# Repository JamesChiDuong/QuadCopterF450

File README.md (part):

# QuadCopter F450 – STM32F429 Flight Controller

Firmware điều khiển quadcopter F450 trên STM32F429I-DISC1 + FreeRTOS: đọc MPU6050, ước lượng góc, PID cascade, trộn 4 motor (X), đọc tay điều khiển RC, arm/disarm và failsafe. Có lệnh UART để test motor, tune PID và xem telemetry.

> ⚠️ **AN TOÀN:** Luôn **tháo cánh quạt** khi test trên bàn, khi đổi cấu hình hoặc nạp firmware mới. Chỉ lắp cánh sau khi đã qua hết checklist ở mục 5.

---

## 0. Chọn phiên bản build

Trong `Core/Inc/USER_Config.h`:

```c
#define FC_VARIANT   FC_VARIANT_RC_FULL     // hoặc FC_VARIANT_UART_TEST, FC_VARIANT_GAMEPAD
```

| | `FC_VARIANT_RC_FULL` (1) | `FC_VARIANT_UART_TEST` (2) | `FC_VARIANT_GAMEPAD` (3) |
|---|---|---|---|
| Thiết bị điều khiển | Tay RC + receiver, RX nối PE2–PE6 | Không có, chỉ lệnh UART | **Tay cầm USB** (GameSir Nova 2 Lite ở chế độ Switch hoặc Xbox…) cắm vào **CN6** |
| Arm | Công tắc CH5 | Lệnh `@QC+ARM` | **Giữ START** 0.5 s |
| Disarm | Gạt CH5 | `@QC+DISARM` | **B** hoặc **BACK** (cả `@QC+DISARM`) |
| Điều khiển | Cần gạt RC | `@QC+SP=...` / bàn phím qua `drone_viewer.py --control` | Cần tay cầm (mục 5, bước 7c) |
| Giới hạn ga | 1850 µs | 1300 µs (chỉ test trên bàn) | 1850 µs |
| Failsafe | Mất sóng RC > 100 ms | Tùy chọn `UART_SP_TIMEOUT_MS` | **Rút / tắt tay cầm** (mất kết nối USB) |
| Màn hình | Các kênh RC | Setpoint UART | Loại tay cầm, trạng thái và vị trí cần |
| Chân dùng thêm | PE2–PE6 | — | PB13/PB14/PB15 (USB), **PC4** (bật nguồn USB) |
| Clock | HSI | HSI | **HSE 8 MHz** (USB cần clock chính xác) |

Muốn giữ nhiều phiên bản mà không phải sửa file: trong CubeIDE tạo thêm Build Configuration, rồi vào *Properties → C/C++ Build → Settings → MCU GCC Compiler → Preprocessor* thêm `FC_VARIANT=2` (hoặc `3`). Dòng lệnh: `make VARIANT=3`. Tương tự, `UI_LCD_ENABLE=0` tắt màn hình.

> ⚠️ **Bản GAMEPAD dùng PC4 để bật nguồn 5 V cho cổng USB CN6** (theo thiết kế của board DISC1). Chân này trước đây là `BLDC3_VCC`. Nếu có dây nào đang cắm vào PC4 thì **rút ra** trước khi nạp bản GAMEPAD.

---

## 1. Phần cứng

| Thành phần | Ghi chú |
|---|---|
| Khung F450, 4× motor A2212/15T 930KV | |
| 4× ESC SimonK 30A | Nhận xung 1000–2000 µs, PWM 400 Hz |
| STM32F429I-DISC1 | SYSCLK 72 MHz (HSI) |
| MPU6050 | I2C2 (100 kHz mặc định, `MPU6050_I2C_SPEED_HZ`) |
| RX 6 kênh (PWM) | 5 kênh được dùng |
| LiPo 3S 2200 mAh, BEC 5V 3A | |

### Sơ đồ chân và đấu nối

Bảng dưới là **đúng những gì firmware đang cấu hình** (đã kiểm tra trong `main.h`, `stm32f4xx_hal_msp.c`, `USER_Motor_Driver.c`, `usbh_conf.c`).

#### a) Cảm biến MPU6050 (module GY-521), I2C2

**Hướng lắp hiện tại:** module nằm ngửa (linh kiện hướng lên), **mũi tên X in trên module chỉ về đuôi máy** (phía M2/M4), trục Y của chip chỉ sang phải (đã đo bằng bài test nghiêng ngày 22/11/2026). Firmware quy đổi: `x_thân = −X_chip, y_thân = +Y_chip, z_thân = −Z_chip` (`IMU_BODY_X/Y/Z` trong `USER_Config.h`; trong file có sẵn công thức cho các hướng lắp khác). Kiểm tra bằng `@QC+DEBUG=1`: ngóc mũi (M1, M3) lên thì **pitch dương**, hạ bên phải (M3, M4) xuống thì **roll dương**, xoay mũi sang phải thì **yaw tăng**.

| Chân module | Chân board | Firmware cấu hình |
|---|---|---|
| VCC | **PF5** | GPIO xuất HIGH (3.3 V) cấp nguồn cho module (hoặc nối thẳng vào chân 3V của board) |
| GND | **PF4** | GPIO xuất LOW (hoặc nối thẳng vào GND của board) |
| SCL | **PF1** | I2C2_SCL, AF4, open-drain, 100 kHz |
| SDA | **PF0** | I2C2_SDA, AF4, open-drain |
| AD0 | để trống / GND | địa chỉ 0x68 (nối VCC thì 0x69, firmware tự dò) |
| INT, XDA, XCL | không nối | — |

```
   GY-521                      STM32F429I-DISC1
   VCC ───────────────────────► PF5   (HIGH)
   GND ───────────────────────► PF4   (LOW)
   SCL ───────────────────────► PF1   (I2C2_SCL)
   SDA ───────────────────────► PF0   (I2C2_SDA)
```

Dây I2C nên ngắn (dưới khoảng 20–30 cm) và tránh đi song song với dây motor.

#### b) 4 ESC → board (cáp servo 3 sợi của mỗi ESC)

| Motor | Vị trí / chiều quay | Giắc servo cắm vào header | Dây **tín hiệu** (trắng/vàng) | Dây **đỏ +5 V** (chân giữa, firmware để **Hi-Z**) | Dây **GND** (đen/nâu) → chân xuất **LOW** |
|---|---|---|---|---|---|
| M1 | trước-trái, **CW** | P1-25 / 27 / 29 | **PB4** (TIM3 CH1) | PG15 | **PG13** |
| M2 | sau-trái, **CCW** | P1-53 / 55 / 57 | **PA8** (TIM1 CH1) | PC8 | **PC6** |
| M3 | trước-phải, **CCW** | **P2-28 / 30 / 32** (đã dời) | **PB0** (TIM3 CH3) | **PB2** | **PF11** |
| M4 | sau-phải, **CW** | P2-48 / 46 / 44 | **PB10** (TIM2 CH3) | PE14 | **PE12** |

Giắc servo 3 chân cắm vào **3 chân cùng hàng liên tiếp** của header (số chân n, n+2, n+4). **M3 đã được dời** từ P2-24/26/28 (PA6 / PC4 / PB0) sang **P2-28/30/32 (PB0 / PB2 / PF11)**: giắc dịch sang một nấc và **xoay ngược 180°** (tín hiệu ở P2-28, GND ở P2-32), vì PC4 là chân bật nguồn USB ở bản GAMEPAD và luôn bị giữ LOW, nên sẽ chập dây đỏ 5 V của ESC. PB2 chịu được 5 V (FT). Muốn đổi chân, sửa bảng `ESCx_GND_*` / `ESCx_VCC_*` trong `USER_Config.h`.

```
   ESC (cáp servo)                 STM32F429I-DISC1
   trắng/vàng (tín hiệu) ───────► PB4 / PA8 / PB0 / PB10
   đỏ        (+5 V BEC)  ───────► chân giữa của giắc (PG15 / PC8 / PB2 / PE14), firmware để Hi-Z
   đen/nâu   (GND)       ───────► chân LOW (PG13 / PC6 / PF11 / PE12)  hoặc GND của board
```

> ⚠️ **Ba điều phải đúng khi nối ESC:**
> 1. **Dây GND của ESC phải vào chân xuất LOW** (cột "GND" ở bảng trên) **hoặc một chân GND thật của board**, không bao giờ vào chân xuất HIGH. Ví dụ với M1: GND vào **PG13**, không phải PG15 (PG15 đang được firmware kéo lên 3.3 V). Muốn đổi chân, sửa code trước rồi mới nối dây.
> 2. **Dây đỏ +5 V của ESC là nguồn do ESC phát ra** (khi cắm pin), không phải đầu vào. Nếu tách được dây thì để trống là tốt nhất. Với giắc 3 chân liền khối, dây đỏ nằm trên chân giữa: chân đó **phải là chân chịu được 5 V (FT) và được firmware để ở Hi-Z**. Bảng trên đã đảm bảo điều này; **tuyệt đối không** đặt chân giữa lên một chân đang xuất HIGH hay LOW (ví dụ PC4 ở bản GAMEPAD).
> 3. Các chân "VCC" cũ (PG15, PC8, PC4, PE14) **đã được tắt trong firmware** (chuyển sang input trở kháng cao, `MOTOR_ESC_VCC_PINS_HIGH = 0`). Trước đây chúng bị kéo HIGH: nếu dây đỏ 5 V của ESC cắm vào đó thì khi cắm pin, 5 V đấu với 3.3 V và **MCU bị reset**. Không cần nối gì vào các chân này.
>
> Khi khởi động, firmware in `> Reset cause: ...` ra UART. Nếu thấy `BOR(brown-out...)` sau khi cắm pin, nghĩa là nguồn 3.3 V bị sụt: kiểm tra lại dây GND và dây đỏ của ESC.
>
> Thiếu chân GND trên board thì gom 4 dây GND của ESC lại (domino hoặc breadboard) rồi nối vào **một** chân GND của header P1/P2. Cách này chắc chắn hơn dùng GPIO làm GND.

Phía động lực của ESC: 2 dây to đỏ/đen vào pin 3S (qua tấm phân phối nguồn của khung F450 / giắc XT60), 3 dây pha vào motor. Thứ tự 3 dây pha không quan trọng; đảo 2 dây thì đổi chiều quay (xem mục 5, bước 6).

#### c) Receiver RC (bản RC FULL)

| Kênh RX | Chân board | Ghi chú |
|---|---|---|
| CH1 aileron (roll) | **PE2** | EXTI hai sườn |
| CH2 elevator (pitch) | **PE3** | |
| CH3 throttle | **PE4** | |
| CH4 rudder (yaw) | **PE5** | |
| CH5 công tắc ARM | **PE6** | |
| GND / +5 V của RX | GND / 5V của board | **GND phải nối chung** với board |

PE2–PE6 là chân trống trên header P1 của board (đã đối chiếu UM1670, bảng 7). Bản UART TEST và GAMEPAD không dùng các chân này.

#### d) Các kết nối khác

| Chức năng | Chân / cổng | Ghi chú |
|---|---|---|
| Nạp code + terminal UART | Cổng **CN1 mini-USB "USB ST-LINK"** (USART1 PA9/PA10 nối sẵn trên board) | 115200 8N1, cổng COM ảo |
| Tay cầm USB (bản GAMEPAD) | Cổng **CN6 micro-USB "USB USER"** qua cáp OTG; PB14 D−, PB15 D+, PB13 VBUS, **PC4** bật nguồn 5 V | **Không** cắm máy tính vào CN6 ở bản GAMEPAD (board xuất 5 V ra cổng này) |
| LCD ILI9341 | SPI5: PF7 SCK, PF9 SDA, PC2 CS, PD13 D/C | Có sẵn trên board, không cần đi dây |
| LED trạng thái | PG14 (LED đỏ LD4) | |
| Nguồn board khi bay | Chân **5V** + **GND** từ BEC 5V 3A | |

#### e) Chân đang bị dùng chung / cần tránh

| Chân | Dùng cho | Lưu ý |
|---|---|---|
| **PC4** | Bật nguồn USB (bản GAMEPAD); trước đây là `BLDC3_VCC` | **Không cắm gì vào PC4** (M3 đã dời sang PB2/PF11) |
| PB2 | Chân giữa (5 V) của giắc M3 | Cũng là chân BOOT1; chỉ có tác dụng khi BOOT0 = 1, nên không ảnh hưởng khởi động |
| PF11 | GND của M3 | Cũng là chân SDRAM trên board; an toàn vì firmware không dùng SDRAM |
| PG15, PE12, PE14, PF4, PF5, PF0, PF1 | Motor/MPU **và** chân SDRAM trên board | An toàn vì firmware không dùng SDRAM |
| PG13 | GND của M1 **và** LED xanh LD3 | LED xanh tắt là bình thường |
| PA8 | Tín hiệu M2 **và** I2C3 của màn cảm ứng (có điện trở kéo lên trên board) | Không ảnh hưởng xung PWM |

**Về màn hình:** LCD của DISC1 bình thường chạy LTDC + SDRAM, nhưng các chân đó đã được dùng cho motor (PB0, PB10, PA6, PC6, PE12, PE14, PG15) và MPU6050 (PF0, PF1, PF4, PF5). Vì vậy firmware ghi thẳng vào GRAM của ILI9341 qua SPI5. SPI5 nằm trên APB2 = 4.5 MHz nên SCK chỉ được 2.25 MHz; giao diện vì thế chỉ vẽ lại phần thay đổi. Nếu ảnh bị lật hoặc ngược, đổi `LCD_MADCTL_VALUE` trong `USER_Config.h`.

```
        M1 (FL, CW)    M3 (FR, CCW)
                 \  ▲  /
                  \ │ /      ▲ = mũi (hướng bay tới)
                  /   \
                 /     \
        M2 (BL, CCW)   M4 (BR, CW)
```

Chiều quay theo khung thực tế (kiểu "props out"): **M1, M4 quay CW; M2, M3 quay CCW** (nhìn từ trên xuống). Cột yaw của mixer (`MIX_Mx_YAW` trong `USER_Config.h`) đã được đặt theo chiều quay này: muốn mũi quay sang phải thì tăng tốc cánh CCW (M2, M3). Nếu sau này đổi chiều cánh, đổi dấu cột yaw.

---

## 2. Kiến trúc firmware

```
Task BLDCTask (High, 250 Hz)          Task UARTTask (Normal)   Task systemTask   Task uiTask (BelowNormal, 10 Hz)
  MPU6050 → đổi trục FRD                 lệnh @QC+...            LED trạng thái     LCD: trạng thái, chân trời
  → Attitude (complementary filter)      telemetry 20 Hz                            nhân tạo, motor, RC/setpoint
  → state machine (arm/disarm/failsafe)
  → PID góc (P) → PID tốc độ góc (PID)
  → Mixer Quad-X → ESC (µs)
```

### Màn hình LCD

```
+------------------------------+
| QUAD F450           RC FULL  |  tiêu đề + phiên bản build
| DISARMED                     |  trạng thái (vàng / xanh lá ARMED / đỏ FAILSAFE / cyan CALIB)
| +----------+  ROLL   -12.3   |
| |  ---o--- |  PITCH    4.5   |  chân trời nhân tạo + góc
| +----------+  YAW     30.0   |
| M1 1500 [########        ]   |  4 thanh motor (xanh lá khi ARMED)
| RC INPUT / UART SETPOINT     |
| last event                   |
| dt 4.0ms  IMU err 0          |
+------------------------------+
```

Quy ước trục (FRD): **roll > 0** là cánh phải chúi xuống, **pitch > 0** là ngóc mũi lên, **yaw > 0** là mũi quay sang phải.

| File (Core/) | Vai trò |
|---|---|
| `Inc/USER_Config.h` | **Mọi tham số chỉnh được**: gain PID, giới hạn, trục IMU, dấu mixer, kênh RC |
| `Src/USER_System.c` | Lõi điều khiển bay: state machine, vòng cascade, an toàn |
| `Src/USER_Attitude.c` | Hiệu chuẩn gyro, complementary filter |
| `Src/USER_PID.c` | PID (dt tường minh, anti-windup, D-on-measurement + lọc) |
| `Src/USER_Mixer.c` | Trộn Quad-X, ưu tiên giữ thăng bằng khi bão hòa |
| `Src/USER_Motor_Driver.c` | Xuất xung ESC theo µs, tự tính prescaler từ clock thật |
| `Src/USER_RC.c` | Đọc RX bằng EXTI + bộ đếm DWT (không tốn timer) |
| `Src/USER_MPU.c` | Driver MPU6050 |
| `Src/USER_Protocol.c` | Lệnh terminal |
| `Src/USER_DataCollect.c` | Telemetry |
| `Src/USER_LCD.c`, `Src/USER_Font8x8.c` | Driver ILI9341 qua SPI5 + font 8×8 |
| `Src/USER_UI.c` | Giao diện màn hình (task riêng, priority thấp) |
| `Src/USER_Gamepad.c` | Bản GAMEPAD: driver tay cầm USB (XInput / Xbox One / HID), task USB, chuyển clock sang HSE |
| `Src/usbh_conf.c`, `Inc/usbh_conf.h` | Lớp nối thư viện ST USB Host với cổng OTG CN6 (PB13–15, PC4) |

### Những gì đã sửa so với bản trước

- **PID chưa bao giờ chạy:** `PID_Gyro_Init` nhận struct theo giá trị nên PID trỏ vào biến tạm, gain bằng 0, và `Sys_InnerLoop` không được gọi ở đâu.
- **Tần số PWM sai:** TIM2/TIM3 chạy 18 MHz chứ không phải 9 MHz, nên "50 Hz" thực ra là 100 Hz. Đây chính là hiện tượng "motor 2 khác các motor còn lại" ghi ở slide 12. Giờ tất cả là 400 Hz, độ phân giải 1 µs.
- **Không có ước lượng góc:** trước đây giá trị gyro (°/s) bị in ra như góc.
- **I2C:** `MPU6050_I2C_ReInit` chỉ DeInit mà không Init lại, nên một lỗi BUSY làm I2C chết hẳn. Đã bỏ việc in lỗi ở mỗi lần đọc. DLPF đổi từ 260 Hz xuống 42 Hz để lọc rung motor. Dải đo gyro tăng lên ±500 °/s.
- **Lỗi khai báo:** thiếu `<stdint.h>` trong ring buffer, `RTOSmalloc` thiếu khai báo.
- **Mới thêm:** đọc RC, arm/disarm, failsafe, lệnh tune PID, telemetry, LED trạng thái.

Bản gốc đã được sao lưu tại `Code/_backup_Core_2026-11-21/`.

---

## 3. Build & nạp

### 3.1 Build

**Cách A – dòng lệnh (MSYS2), đã dùng để build và nạp thử trên board:**

```bash
# Cài 1 lần (trong terminal MSYS2 UCRT64):
pacman -S --needed mingw-w64-ucrt-x86_64-arm-none-eabi-gcc mingw-w64-ucrt-x86_64-arm-none-eabi-newlib make

# Build (đứng trong thư mục "Code/1. Control BLDC"):
export PATH=/c/msys64/ucrt64/bin:/c/msys64/usr/bin:$PATH
make -j8 DIRECT_LD=1                # bản RC FULL      -> build/quadcopter.bin
make -j8 DIRECT_LD=1 VARIANT=2      # bản UART TEST
make clean                          # khi đổi VARIANT hoặc UI, clean trước rồi build lại
```

`DIRECT_LD=1` chỉ cần trên máy bật **Smart App Control**: chính sách này chặn `collect2.exe` và `arm-none-eabi-size.exe` của MSYS2. Khi đó `tools/gcc-link.sh` gọi thẳng `arm-none-eabi-ld.exe` (không bị chặn) với đúng tham số gcc định dùng. Trên máy khác chỉ cần `make`.

**Cách A2 – Keil MDK (Arm Compiler 6), dùng trên máy phát triển từ 23/11/2026.** Từ ngày này, Smart App Control chặn luôn `arm-none-eabi-gcc.exe` của MSYS2. Bộ trình biên dịch của Keil do Arm ký số nên vẫn chạy được:

```bash
# đứng trong "Code/1. Control BLDC", cần Keil MDK tại C:\Keil_v5
sh tools/keil/build_keil.sh 3                       # bản GAMEPAD   -> build_keil/quadcopter.bin
sh tools/keil/build_keil.sh 1                       # bản RC FULL
sh tools/keil/build_keil.sh 3 1 "-DGPS_ENABLE=1"    # thêm cờ -D (ví dụ bật GPS)
```

Script dùng `tools/keil/startup_armclang.s` (sinh tự động từ file startup GCC, bảng vector giữ nguyên), `tools/keil/quadcopter.sct` và thư viện microlib (`printf` đi qua hàm `fputc()` trong `main.c`). Makefile GCC giữ nguyên để dùng trên máy khác.

**Cách B – STM32CubeIDE:** mở workspace `Code/` → project **1. Control BLDC** → Build. Các file `.c` mới trong `Core/Src` được tự động thêm vào build. Nếu mở lại `.ioc` và generate code, mọi thay đổi đã nằm trong vùng `USER CODE` hoặc đã được ghi vào `.ioc`, nên không bị mất.

### 3.2 Nạp (không cần driver)

ST-LINK/V2-1 trên DISC1 hiện ra như một **ổ USB tên `DIS_F429ZI`**. Chỉ cần:

1. Cắm cổng **USB ST-LINK (mini-USB, CN1)** vào PC.
2. Kéo-thả (hoặc copy) `build/quadcopter.bin` vào ổ `DIS_F429ZI`.
3. Đèn LD1 (COM) nháy đỏ/xanh trong lúc nạp; ổ đĩa tự ngắt rồi gắn lại; chip tự reset và chạy firmware mới.
4. Nạp **thành công** khi trong ổ **không có** file `FAIL.TXT`. Nếu có, mở file đó để xem lý do.

```powershell
Copy-Item "Code\1. Control BLDC\build\quadcopter.bin" E:\     # E: = ổ DIS_F429ZI
```

Các cách khác: CubeIDE (Run/Debug) hoặc STM32CubeProgrammer. Cả hai đều cần **driver ST-LINK (STSW-LINK009)**; trên máy phát triển, Device Manager đang báo "ST-Link Debug" lỗi mã 28 vì chưa có driver này. Nạp kéo-thả thì không cần.

---

## 4. Lệnh terminal (USART1, 115200, kết thúc bằng `\r\n`)

| Lệnh | Ý nghĩa |
|---|---|
| `@QC+HELP` | Danh sách lệnh ngắn gọn |
| `@QC+HELP=<TÊN>` | Cú pháp chi tiết và ví dụ của một lệnh, ví dụ `@QC+HELP=PID` |
| `@QC+LIST` | **Toàn bộ lệnh** kèm cú pháp, tham số, ví dụ và phiên bản build dùng được |
| `@QC+STATUS` | Trạng thái, góc, RC, motor, thời gian vòng lặp |
| `@QC+DEBUG=<n>` | Stream 20 Hz: 0 tắt, 1 góc, 2 RC, 3 motor, 4 PID roll/pitch, 5 PID yaw, 6 dòng `$TLM` cho `drone_viewer.py` |
| `@QC+CALIB` | Hiệu chuẩn lại gyro (để yên khung) |
| `@QC+LEVEL` | Lấy tư thế hiện tại làm "mặt phẳng" (chỉ lưu RAM) |
| `@QC+PID?` | Xem toàn bộ gain |
| `@QC+PID=RR,0.7,0.5,0.015` | Đặt gain: `RA`/`PA` góc roll/pitch, `RR`/`PR`/`YR` tốc độ góc roll/pitch/yaw |
| `@QC+CONTROL_MOTOR=<1..4\|5>,<µs>` | Test motor khi DISARMED (tối đa 1500 µs, 5 = cả 4 motor). **Tháo cánh!** |
| `@QC+STOP_MOTOR` | Tắt mọi motor test |
| `@QC+SP=<thr>,<roll>,<pitch>,<yawrate>` | Setpoint (chỉ ở bản UART TEST, ga tối đa 1300 µs) |
| `@QC+ARM` / `@QC+DISARM` | Arm (chỉ ở bản UART TEST) / Disarm (luôn có hiệu lực, mọi bản) |
| `@QC+PADTEST=1` / `=0` / `?` | Bản GAMEPAD: **test cần gạt → motor** không cần MPU6050 và không cần arm (mở vòng, qua mixer). LCD hiện `STICK TEST` màu tím. Ga ≤ 1050 µs thì motor đứng yên, tối đa 1500 µs. Dừng bằng `PADTEST=0`, B/BACK, `DISARM`, `STOP_MOTOR` hoặc rút tay cầm. **THÁO CÁNH** |
| `@QC+PADLOG=1` / `=0` | Bản GAMEPAD: in nút bấm và chuyển động cần gạt khi có thay đổi (mặc định bật) |
| `@QC+GPTEST` | Bản GAMEPAD: tự kiểm tra bộ giải mã HID/XInput ngay trên chip (rút tay cầm trước khi chạy) |

Lệnh `@QC+SRC` đã bị bỏ: nguồn điều khiển giờ cố định theo phiên bản build (mục 0).

**Lưu ý: `CONTROL_MOTOR` đã đổi cú pháp.** Trước đây là `<motor>,<tần số>,<duty %>`, giờ là `<motor>,<độ rộng xung µs>`.

Gain chỉnh bằng lệnh chỉ lưu trong RAM. Khi đã tìm được bộ gain tốt, hãy ghi vào `USER_Config.h`.

### Mô phỏng / viewer 3D bằng Python (`host/`)

#### Các file

| File | Vai trò | Cần thư viện ngoài? |
|---|---|---|
| `fc_model.py` | Bản port từng dòng của bộ điều khiển firmware (PID, bộ lọc góc, mixer, arm/disarm, giữ vị trí GPS) và **mô hình vật lý 6 bậc tự do của khung F450**. Hằng số (gain, giới hạn, dấu mixer) được **đọc trực tiếp từ `USER_Config.h`** | Không |
| `sim_flight_controller.py` | **Test hồi quy tự động**: bộ điều khiển chạy vòng kín với mô hình vật lý, in `ok` hoặc `FAIL` cho từng mục | Không |
| `drone_viewer.py` | Viewer 3D: xem tư thế máy thật qua UART, lái bằng bàn phím, hoặc bay mô phỏng | `vpython`, `pyserial`, `numpy` |
| `3D-Visualize.py` | Script cũ, dùng với `DEBUG=1` | `vpython`, `pyserial` |

#### Cài đặt

1. Cài **Python 3.9 trở lên** từ python.org, nhớ tick "Add python.exe to PATH". Trên máy phát triển, lệnh `python` mặc định chỉ là lối tắt mở Microsoft Store; đã dùng thay bằng `C:\msys64\ucrt64\bin\python.exe` (3.14).
2. Kiểm tra: `python --version`.
3. Chỉ khi cần **viewer 3D**: `pip install -r host/requirements.txt`. Hai bài test bên dưới **không cần** bước này.

Mọi lệnh chạy từ thư mục gốc dự án (`QuadCorter Project`).

#### Test 1: test hồi quy bộ điều khiển (chạy trước mỗi lần nạp code)

```
python host/sim_flight_controller.py
```

Chạy khoảng 20–40 giây. Kết quả đúng (đã chạy ngày 24/11/2026):

```
Unit checks
  ok  : +roll -> left motors (M1, M2) faster [...]
  ok  : +pitch -> front motors (M1, M3) faster [...]
  ok  : saturation keeps differential [2000, 2000, 1600, 1600]
  ok  : PID P+I first step
Attitude control (250 Hz loop, rigid body held in the air)
  ok  : arm with throttle low
  ok  : recover 10/-8 deg -> err 0.17/0.28 deg
  ok  : track roll 20 / pitch -15 -> err 0.06/0.03, peak 20.0
  ok  : yaw rate 90 dps -> err 1.63 dps
  ok  : back to level -> 0.01 0.01 0.87
Take-off and hover (full 6-DOF model)
  ok  : climbs with throttle 1437 us -> altitude 2.25 m
  ok  : stays level near hover: err 0.00/0.00 deg, drift 0.00 m
  ok  : nose down 10 deg -> moves forward 2.41 m
GPS position hold (USER_PosHold.c port, 5 Hz noisy GPS)
  ok  : nose    0 deg: 5 m push -> back within 0.02 m, max tilt sp 8.6 deg
  ok  : nose   90 deg: 5 m push -> back within 0.02 m, max tilt sp 9.0 deg
  ok  : nose -135 deg: 5 m push -> back within 0.02 m, max tilt sp 10.5 deg
  ok  : 3 m/s side wind, 25 s -> holds within 0.01 m (...)
  ok  : heading 180 deg wrong -> runs away (31.6 m), test is meaningful
Negative control
  ok  : wrong roll sign diverges (peak ... deg, state FAILSAFE)
Telemetry parser
  ok  : parse $TLM
  ok  : parse legacy attitude line

ALL PASSED
```

Ý nghĩa từng nhóm:

| Nhóm | Kiểm tra gì | Nếu FAIL thì nghĩ tới |
|---|---|---|
| Unit checks | Dấu cột `MIX_Mx_ROLL/PITCH` đúng với vị trí motor; mixer dồn ga khi bão hòa; phép tính PID | Sai dấu trong bảng mixer của `USER_Config.h` |
| Attitude control | Khung treo trên gimbal (chỉ xoay): tự về thăng bằng sau khi bị nghiêng 10°, bám góc đặt, bám tốc độ yaw | Gain PID quá cao hoặc quá thấp, sai dấu cột yaw (`MIX_Mx_YAW`) |
| Take-off and hover | Mô hình đầy đủ có trọng lực: cất cánh, giữ thăng bằng, chúi mũi thì bay tới | Sai quy ước dấu pitch, giới hạn ga |
| GPS position hold | Giữ vị trí với GPS 5 Hz có nhiễu, ở 3 hướng mũi khác nhau và khi có gió ngang 3 m/s | Gain `POSHOLD_*`, công thức xoay theo hướng mũi trong `USER_PosHold.c` |
| Negative control | **Cố tình làm sai** (đảo dấu roll, sai hướng 180°) và yêu cầu máy **phải mất ổn định** | Nếu nhóm này FAIL thì mô phỏng không đủ nhạy để bắt lỗi; các test khác không còn đáng tin |
| Telemetry parser | Đọc đúng dòng `$TLM` và dòng `DEBUG=1` | Định dạng in trong `USER_DataCollect.c` đã đổi |

- Dòng cuối là `ALL PASSED` hoặc `FAILED (n)`. Mã thoát là 0 hoặc 1, nên dùng được trong script.
- Muốn thử một file cấu hình khác: `python host/sim_flight_controller.py đường/dẫn/USER_Config.h`.
- **Quy trình khi sửa code điều khiển:**
  1. Sửa `USER_Config.h` (gain, giới hạn, dấu mixer, `POSHOLD_*`).
  2. Chạy test này, phải ra `ALL PASSED`.
  3. Mới build và nạp.

  Nếu sửa **thuật toán** trong file C (`USER_PID.c`, `USER_Attitude.c`, `USER_Mixer.c`, `USER_PosHold.c`, `USER_System.c`), phải sửa **đúng như vậy** trong `fc_model.py`. Mô phỏng chỉ kiểm tra được bản port Python, không đọc trực tiếp code C.
- Test đạt nghĩa là **dấu đúng và gain hợp lý trên một mô hình ước lượng** (khung 450 mm, khối lượng 1.2 kg, lực đẩy motor ước lượng…). Nó **không thay thế** bài test trên bàn (tháo cánh) và test buộc dây.

#### Test 2: tự kiểm tra viewer (không mở cửa sổ)

```
python host/drone_viewer.py --selftest
```

Kiểm tra phần logic của viewer mà không cần vpython hay board: phím bấm ra lệnh đúng chiều (mũi tên lên = chúi mũi, D = yaw phải), nguồn mô phỏng arm được, cất cánh, nghiêng phải thì trôi sang Đông, rồi disarm. Kết quả đúng kết thúc bằng `SELFTEST PASSED`.

#### Test 3: bay mô phỏng có hình 3D (không cần board)

```
python host/drone_viewer.py --sim
```

Cần `pip install -r host/requirements.txt`. Bộ điều khiển firmware (bản port) và vật lý F450 chạy trên PC; bạn lái bằng bàn phím như lái máy thật. Đã chạy được trên máy phát triển ngày 24/11/2026.

> **Trên máy phát triển** (Smart App Control chặn `numpy` của MSYS2), viewer chạy bằng **Python đi kèm KiCad 8**, trong môi trường ảo `host/.venv` đã cài sẵn `vpython` và `pyserial`:
> ```
> host\.venv\Scripts\python.exe host\drone_viewer.py --sim
> host\.venv\Scripts\python.exe host\drone_viewer.py --port COM4
> ```
> Cách tạo lại môi trường ảo nếu bị xóa:
> ```
> "%LOCALAPPDATA%\Programs\KiCad\8.0\bin\python.exe" -m venv --system-site-packages host\.venv
> host\.venv\Scripts\python.exe -m pip install vpython pyserial
> ```
> Nếu trình duyệt không tự mở, xem cổng trong `netstat -ano` của tiến trình `pythonw` rồi mở `http://localhost:<cổng>`. Đóng tab trình duyệt thì viewer tự thoát.

1. Click vào khung 3D trong trình duyệt để nó nhận bàn phím.
2. `SPACE` để arm, `H` để đưa ga về mức hover, `W/S` tăng/giảm ga.
3. Mũi tên để nghiêng (lên = bay tới), `A/D` để xoay.
4. `R` để reset, `Q` để thoát.

#### Test 4: xem máy thật real-time

```
python host/drone_viewer.py --port COM4             # drone 3D xoay theo tư thế đọc từ UART
python host/drone_viewer.py --port COM4 --control   # + lái bằng bàn phím (firmware bản UART TEST, THÁO CÁNH)
```

Đóng mọi terminal đang mở COM4 trước khi chạy.

#### Ghi chú

- Viewer mở trong trình duyệt (vpython). Click vào khung 3D trước để nó nhận bàn phím.
- Phím: `SPACE` arm, `X` disarm, `W/S` tăng/giảm ga, mũi tên = pitch/roll, `A/D` = yaw, `H` ga hover (sim), `C` calib, `L` level, `R` reset (sim), `Q` thoát (tự gửi DISARM).
- Ở chế độ live, script tự gửi `@QC+DEBUG=6`. Cánh quạt đổi màu theo công suất motor (xanh dương đến đỏ).
- Ở chế độ `--control`, setpoint chỉ được gửi khi thay đổi, cộng thêm 1 lần mỗi giây; ga bị giới hạn theo `UART_SP_THROTTLE_MAX_US`.
- `fc_model.py` là bản port của bộ điều khiển firmware và đọc hằng số trực tiếp từ `USER_Config.h`. Đổi gain trong file đó thì mô phỏng dùng ngay gain mới.
- `3D-Visualize.py` (script cũ) vẫn dùng được với `DEBUG=1`.

---

## 5. Hướng dẫn test từng bước

Làm **theo đúng thứ tự**; chỉ sang bước sau khi bước trước đạt. Bước 1–5 chỉ cần cáp USB, **chưa cắm pin LiPo**. Từ bước 6 trở đi **tháo hết cánh quạt**.

LED đỏ LD4 cho biết trạng thái: **nháy nhanh** = CALIBRATING, **nháy chậm** = DISARMED, **sáng liên tục** = ARMED, **nháy đôi** = FAILSAFE.

### Bước 1 – Mở terminal

- Cổng: **USB Serial Device (COMx)** trong Device Manager. Đó là cổng ảo của ST-LINK, nối vào USART1 (PA9/PA10); trên máy phát triển là **COM4**.
- Cấu hình **115200, 8N1**, gửi kèm **CR+LF** (`\r\n`). Dùng PuTTY, Tera Term, Serial Monitor của VS Code, hoặc Arduino Serial Monitor (chọn "Both NL & CR").
- Nhấn nút **RESET (đen)** trên board để xem log khởi động.

**Đạt** khi thấy (log thật, đã chạy trên board):
```
> Build variant: RC FULL
> Motor init: holding 1000 us for 3000 ms (ESC arming)...
> Checking MPU6050 (I2C2 PF1=SCL PF0=SDA, 100000 Hz)...
> I2C2: device found at 0x68                       <- chỉ có khi đã nối MPU6050 (bước 3)
> MPU6050 configured (addr 0x68, gyro 65.5 LSB/dps, acc 4096 LSB/g)
ENTER FREERTOS
> Flight task started. Keep the frame still: calibrating gyro...
> QuadCopter FC ready. Send @QC+HELP for commands.
```
Gửi `@QC+HELP`: firmware phải trả về danh sách lệnh và `@ Command OK !!`.

**Không thấy gì?** Kiểm tra đúng cổng COM, đúng baud, rồi nhấn RESET. Nếu vẫn không có gì, nạp lại (mục 3.2) và kiểm tra ổ đĩa có `FAIL.TXT` không.

### Bước 2 – Màn hình LCD

Ngay sau khi khởi động, LCD phải hiện:

- thanh tiêu đề xanh đậm `QUAD F450` cùng `RC FULL` (hoặc `UART TEST`);
- trạng thái `CALIBRATING` màu cyan;
- khung chân trời nhân tạo, các nhãn `ROLL / PITCH / YAW`;
- 4 dòng `M1..M4 1000` kèm thanh xám;
- dòng sự kiện ở cuối màn hình.

| Hiện tượng | Xử lý |
|---|---|
| Trắng xóa / đen hoàn toàn | Board chưa nhận lệnh SPI. Nhấn RESET; kiểm tra `UI_LCD_ENABLE = 1`. Nếu vẫn vậy, báo lại kèm log UART |
| Hình bị lật gương / ngược | Đổi `LCD_MADCTL_VALUE` (thử 0x88, 0x08, 0xC8) |
| Màu đỏ ↔ xanh dương bị đảo | Đổi bit BGR: 0x48 → 0x40 |

### Bước 3 – Nối và kiểm tra MPU6050

Nối module GY-521 (MPU6050) với board:

| MPU6050 | Board |
|---|---|
| VCC | **PF5** (firmware xuất 3.3 V ra chân này) hoặc chân 3V |
| GND | **PF4** (firmware kéo xuống 0 V) hoặc GND |
| SCL | **PF1** |
| SDA | **PF0** |
| AD0 | để trống hoặc GND (0x68); nối VCC thì địa chỉ là 0x69, firmware tự nhận |

Nhấn RESET và đọc log:

| Log | Ý nghĩa |
|---|---|
| `device found at 0x68` + `MPU6050 configured` | **Đạt** |
| `SDA (PF0) has NO pull-up` / `SCL (PF1) has NO pull-up` | Module **chưa được nối hoặc chưa có nguồn** (đây là kết quả lúc kiểm tra trên máy phát triển, khi chưa cắm MPU). Kiểm tra dây VCC/GND |
| `no answer ... NACK` nhưng không có dòng "NO pull-up" | Có dây và có pull-up nhưng không có thiết bị trả lời: SDA/SCL bị đảo, hoặc module hỏng |
| `bus BUSY` / `timeout` | Dây lỏng hoặc chập; rút ra cắm lại rồi RESET |

Có thể cắm MPU **sau khi** đã khởi động: firmware tự dò lại mỗi 2 giây (sự kiện `IMU not found (retrying)` đổi thành `IMU found, calibrating`).

### Bước 4 – Hiệu chuẩn và kiểm tra trục

1. Để board **đứng yên** khoảng 2 s. Trạng thái chuyển `CALIBRATING` → `DISARMED` (LCD đổi sang màu vàng, LED nháy chậm).
2. `@QC+STATUS` phải báo `calibrated=1`, `IMU errors` không tăng nữa, `dt=4.00 ms`.
3. `@QC+DEBUG=1` rồi nghiêng thử board/khung:
   - nghiêng **cánh phải xuống** thì `R` **dương**;
   - **ngóc mũi lên** thì `P` **dương**;
   - **xoay mũi sang phải** thì `Y` **tăng**.

   Nếu sai, sửa `IMU_BODY_X/Y/Z` trong `USER_Config.h`, build và nạp lại. Chân trời trên LCD cũng phải nghiêng ngược chiều với khung, giống đồng hồ chân trời trong buồng lái.
4. Đặt khung trên mặt phẳng, gửi `@QC+LEVEL` (roll/pitch về khoảng 0). Gửi `@QC+DEBUG=0` để tắt stream.

### Bước 5 – Viewer 3D trên PC (tùy chọn)

Cần Python cho Windows (python.org) cùng `pip install -r host/requirements.txt`. **Đóng terminal serial trước**, vì mỗi lúc chỉ một chương trình mở được cổng COM.

```
python host/drone_viewer.py --port COM4
```

Trình duyệt mở cảnh 3D; nghiêng board thì drone trên màn hình nghiêng theo. Không có board thì dùng `--sim`.

### Bước 6 – ESC và motor (cắm pin, THÁO CÁNH)

1. Cắm pin LiPo **sau khi** board đã chạy: ESC kêu bíp xác nhận tín hiệu 1000 µs.
2. Lần lượt: `@QC+CONTROL_MOTOR=1,1150` … `=4,1150`. Mỗi lần chỉ đúng motor đó quay chậm (LCD: thanh `M1` dài ra).
3. Kiểm tra **vị trí** và **chiều quay** đúng sơ đồ: M1 trước-trái **CW**, M2 sau-trái **CCW**, M3 trước-phải **CCW**, M4 sau-phải **CW**. Quay ngược thì đảo 2 trong 3 dây motor.
4. `@QC+STOP_MOTOR` thì mọi motor dừng. Giới hạn test là 1500 µs.

Lệnh test motor chạy được cả khi chưa có MPU6050 (trạng thái CALIBRATING), nhưng không thể arm.

### Bước 7a – Bản RC FULL: tay điều khiển (THÁO CÁNH)

1. Nối RX: CH1→PE2, CH2→PE3, CH3→PE4, CH4→PE5, CH5→PE6, GND chung, nguồn 5 V cho RX.
2. Bật tay điều khiển, gửi `@QC+DEBUG=2`. Phải thấy `RC OK`, mọi kênh trong 1000–2000, ga thấp nhất < 1050, CH5 bật > 1700. Đẩy cần pitch tới thì `SP P` âm; cần roll sang phải thì `SP R` dương. Nếu ngược, đổi `RC_REVERSE_*`.
3. **Arm:** ga về thấp nhất, gạt CH5 lên. LCD hiện `ARMED` màu xanh lá, LED sáng liên tục, motor quay ở mức idle 1100 µs.
4. **Kiểm tra phản ứng** bằng `@QC+DEBUG=3`, ga khoảng 1300:
   - nghiêng khung **sang phải** thì **M3, M4 (bên phải) tăng**;
   - **ngóc mũi lên** thì **M2, M4 (phía sau) tăng**.

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
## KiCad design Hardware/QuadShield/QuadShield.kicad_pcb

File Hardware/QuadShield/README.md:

# QuadShield – mạch đế cho STM32F429I-DISC1 (QuadCopter F450)

Shield 2 lớp, kích thước **66 × 155 mm**, cắm **bên dưới** board DISC1:
- Hai socket cái 2x32 nhận header P1/P2 của DISC1.
- Phần trên của shield (0–119.3 mm) trùng đúng khuôn board DISC1.
- Phần mở rộng phía dưới (119.3–155 mm) chứa các linh kiện cao: XT30, còi, giắc ESC/RC/GPS.

## Chức năng

| Khối | Chi tiết | Chân DISC1 |
|---|---|---|
| Nguồn | XT30 (pin 2S–4S) → PTC 1.5 A → SS34 chống ngược cực → **AP63205** 5 V / 2 A → SS34 (diode OR) → chân 5V của DISC1 | P1-1/2 (5V) |
| ESC ×4 | Giắc 3 chân: **S / để trống / GND**. Dây đỏ 5V của ESC không nối, vì trước đây nó gây reset MCU | M1 PB4 (P1-25), M2 PA8 (P1-53), M3 PB0 (P2-28), M4 PB10 (P2-48) |
| MPU6050 | GY-521 **hàn nằm phẳng** (cao khoảng 5 mm, vừa khe dưới DISC1). **Mũi tên X hướng về đuôi máy**, khớp với `IMU_BODY_*` hiện tại | SDA PF0 (P1-7), SCL PF1 (P1-8), VCC 3V (P2-1) |
| GPS | Giắc 1x6: 5V, TX, RX, SCL, SDA, GND (dạng module M8N) | GPS TX → PD2 (P1-40), GPS RX ← PC12 (P1-43) |
| RC | 5 giắc 3 chân S / + / − | PE2–PE6 |
| Đo áp pin | 100k / 22k + 100 nF (4S 16.8 V cho ra 3.03 V) | PC3 (P2-15) |
| Còi | Còi active 5 V, transistor MMBT3904, diode chống ngược | PD4 (P1-38) |
| Pull-up I2C | R6/R7 4k7 **DNP** (không hàn), vì GY-521 đã có sẵn | |

Nguồn số liệu:
- Pinout và kích thước cơ khí: UM1670 Rev 5 (bảng 7, hình 3–5), file trong `Documents/`.
- Mạch buck: datasheet Diodes DS41326, hình 1 (FB nối VOUT, EN nối VIN, 4.7 µH, Cin 10 µF, Cout 2×22 µF, C BST 100 nF).

## File

| File | Nội dung |
|---|---|
| `design.py` | **Nguồn duy nhất**: linh kiện, footprint, net, bảng chân P1/P2 |
| `gen_sch.py` | Sinh `QuadShield.kicad_sch` (ký hiệu lấy từ thư viện KiCad 8, nối bằng nhãn net) |
| `gen_pcb.py` | Đặt linh kiện, router A* 2 lớp, đổ GND hai mặt, via khâu → `QuadShield.kicad_pcb` |
| `fill_zones.py` | Tô vùng đồng (tách riêng vì `ZONE_FILLER` crash trên board tạo bằng script) |
| `build.ps1` | Chạy cả chuỗi, xuất ERC/DRC. Thêm `-Fab` để xuất Gerber, file khoan, BOM, file vị trí, PDF vào `fab/` |
| `fab/QuadShield-gerbers.zip` | Gói gửi nhà mạch (JLCPCB, PCBWay…) |

Build lại sau khi sửa `design.py` hoặc phần đặt linh kiện (`PLACE`) trong `gen_pcb.py`:

```
powershell -ExecutionPolicy Bypass -File build.ps1 -Fab
```

Kết quả hiện tại (24/11/2026):
- **ERC:** 0 lỗi điện. Có 43 cảnh báo "library not in configuration", sẽ tự hết sau lần đầu mở KiCad.
- **DRC:** 0 vi phạm, 0 pad chưa nối, khớp 100% với schematic.

## Phải kiểm tra trước khi đặt mạch

1. **Mở KiCad → PCB Editor → View → 3D Viewer**, kiểm tra:
   - **Hướng XT30:** miệng cắm phải quay ra mép dưới board.
   - Linh kiện cao không đụng mặt dưới DISC1. Khe hở khoảng 8.5 mm với socket chuẩn.
2. **Đo trên board DISC1 thật bằng đồng hồ:** P1-1 (góc trên, cột ngoài bên trái) phải là **5V**, P2-1 (cột trong bên phải) phải là **3V**. Shield dựa đúng vào điều này.
3. **Socket cái 2x32** phải là loại cao 8.5 mm, chân vuông 0.64 mm (lỗ 1.0 mm). Footprint dùng mẫu pad của *PinHeader* một cách có chủ ý: PinSocket của KiCad bị lật gương (chân 2 nằm ở −x), không đúng khi DISC1 chồng cùng chiều.
4. **Thứ tự chân của module GY-521 và GPS** phải khớp với nhãn in trên board: GY-521 là VCC GND SCL SDA XDA XCL AD0 INT; GPS là 5V TX RX SCL SDA GND. Module GPS khác hãng có thể khác thứ tự.
5. **Mã LCSC:** chỉ có AP63205WU-7 = C2071056 đã được xác minh. Các linh kiện khác chọn khi đặt hàng (BOM trong `fab/`).
6. **Lỗ bắt khung F450 chưa có.** Thêm sau khi đo khung.

## Firmware

Không cần sửa firmware:
- Các chân cũ dùng làm GND hoặc VCC giả (PG13, PC6, PF11, PE12, PF4, PF5…) không nối gì trên shield.
- MPU lấy nguồn 3V thật của board.
- Đo áp pin (PC3) và còi (PD4) cần **thêm code**. Phần này chưa làm.

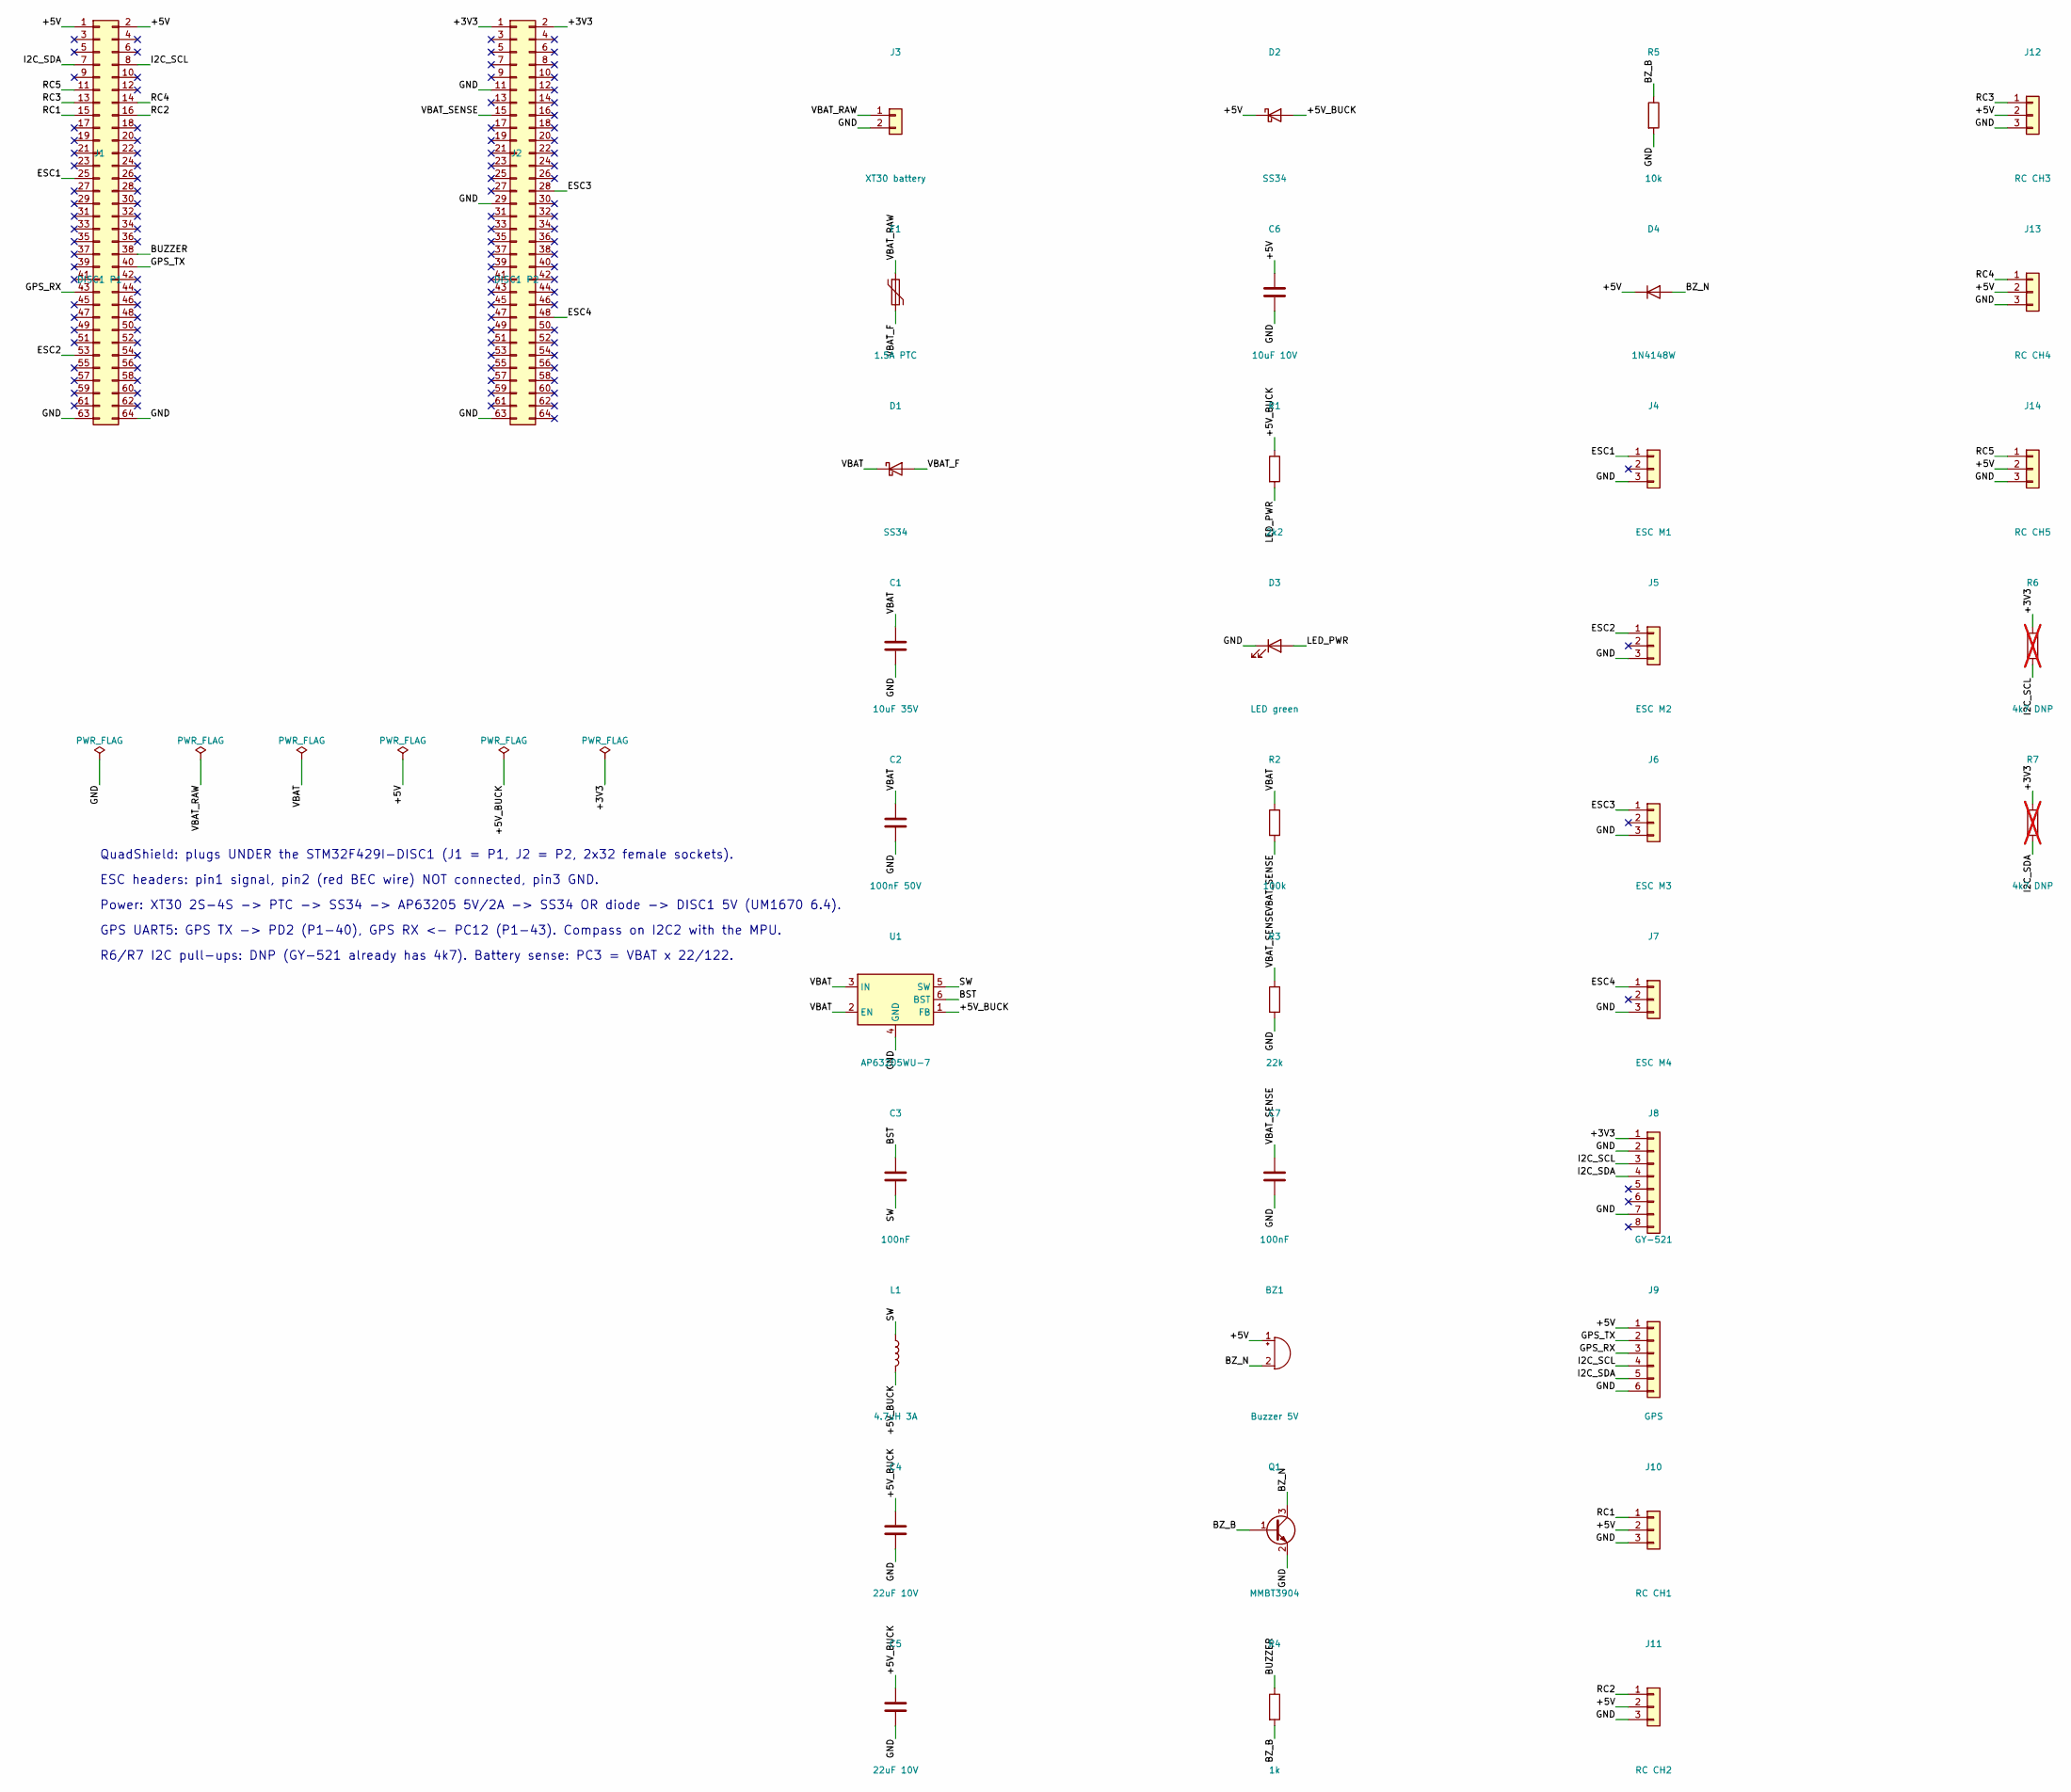
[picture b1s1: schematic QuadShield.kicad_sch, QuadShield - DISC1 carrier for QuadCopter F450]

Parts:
BZ1: Buzzer 5V; Buzzer_12x9.5RM7.6
C1: 10uF 35V; C_1206_3216Metric
C2: 100nF 50V; C_0603_1608Metric
C3, C7: 100nF; C_0603_1608Metric
C4, C5: 22uF 10V; C_1206_3216Metric
C6: 10uF 10V; C_0805_2012Metric
D1, D2: SS34; D_SMA
D3: LED green; LED_0603_1608Metric
D4: 1N4148W; D_SOD-123
F1: 1.5A PTC; Fuse_1812_4532Metric
J1: DISC1 P1; PinHeader_2x32_P2.54mm_Vertical
J2: DISC1 P2; PinHeader_2x32_P2.54mm_Vertical
J3: XT30 battery; AMASS_XT30PW-M_1x02_P2.50mm_Horizontal
J4: ESC M1; PinHeader_1x03_P2.54mm_Vertical
J5: ESC M2; PinHeader_1x03_P2.54mm_Vertical
J6: ESC M3; PinHeader_1x03_P2.54mm_Vertical
J7: ESC M4; PinHeader_1x03_P2.54mm_Vertical
J8: GY-521; PinHeader_1x08_P2.54mm_Vertical
J9: GPS; PinHeader_1x06_P2.54mm_Vertical
J10: RC CH1; PinHeader_1x03_P2.54mm_Vertical
J11: RC CH2; PinHeader_1x03_P2.54mm_Vertical
J12: RC CH3; PinHeader_1x03_P2.54mm_Vertical
J13: RC CH4; PinHeader_1x03_P2.54mm_Vertical
J14: RC CH5; PinHeader_1x03_P2.54mm_Vertical
L1: 4.7uH 3A; L_Taiyo-Yuden_NR-50xx
Q1: MMBT3904; SOT-23
R1: 2k2; R_0603_1608Metric
R2: 100k; R_0603_1608Metric
R3: 22k; R_0603_1608Metric
R4: 1k; R_0603_1608Metric
R5: 10k; R_0603_1608Metric
R6, R7: 4k7 DNP; R_0603_1608Metric; not fitted
U1: AP63205WU-7; TSOT-23-6; LCSC C2071056

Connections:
/+3V3: J2.1, J2.2, J8.1, R6.1, R7.1
/+5V: BZ1.1 (+), C6.1, D2.1 (K), D4.1 (K), J1.1, J1.2, J9.1, J10.2, J11.2, J12.2, J13.2, J14.2
/+5V_BUCK: C4.1, C5.1, D2.2 (A), L1.2, R1.1, U1.1 (FB)
/BST: C3.1, U1.6 (BST)
/BUZZER: J1.38, R4.1
/BZ_B: Q1.1 (B), R4.2, R5.1
/BZ_N: BZ1.2 (-), D4.2 (A), Q1.3 (C)
/ESC1: J1.25, J4.1
/ESC2: J1.53, J5.1
/ESC3: J2.28, J6.1
/ESC4: J2.48, J7.1
/GND: C1.2, C2.2, C4.2, C5.2, C6.2, C7.2, D3.1 (K), J1.63, J1.64, J2.11, J2.29, J2.63, J3.2, J4.3, J5.3, J6.3, J7.3, J8.2, J8.7, J9.6, J10.3, J11.3, J12.3, J13.3, J14.3, Q1.2 (E), R3.2, R5.2, U1.4 (GND)
/GPS_RX: J1.43, J9.3
/GPS_TX: J1.40, J9.2
/I2C_SCL: J1.8, J8.3, J9.4, R6.2
/I2C_SDA: J1.7, J8.4, J9.5, R7.2
/LED_PWR: D3.2 (A), R1.2
/RC1: J1.15, J10.1
/RC2: J1.16, J11.1
/RC3: J1.13, J12.1
/RC4: J1.14, J13.1
/RC5: J1.11, J14.1
/SW: C3.2, L1.1, U1.5 (SW)
/VBAT: C1.1, C2.1, D1.1 (K), R2.1, U1.2 (EN), U1.3 (IN)
/VBAT_F: D1.2 (A), F1.2
/VBAT_RAW: F1.1, J3.1
/VBAT_SENSE: C7.1, J2.15, R2.2, R3.1

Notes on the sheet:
QuadShield: plugs UNDER the STM32F429I-DISC1 (J1 = P1, J2 = P2, 2x32 female sockets).
ESC headers: pin1 signal, pin2 (red BEC wire) NOT connected, pin3 GND.
Power: XT30 2S-4S -> PTC -> SS34 -> AP63205 5V/2A -> SS34 OR diode -> DISC1 5V (UM1670 6.4).
GPS UART5: GPS TX -> PD2 (P1-40), GPS RX <- PC12 (P1-43). Compass on I2C2 with the MPU.
R6/R7 I2C pull-ups: DNP (GY-521 already has 4k7). Battery sense: PC3 = VBAT x 22/122.

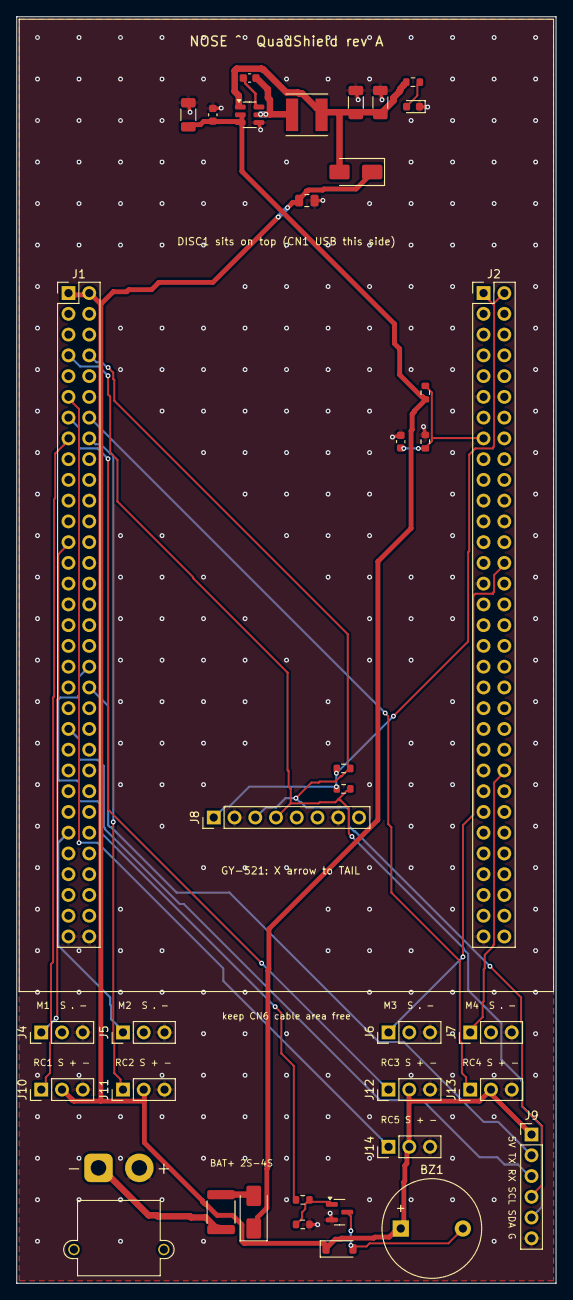
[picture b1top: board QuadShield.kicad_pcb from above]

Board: 2 copper layers, 66.0 x 155.0 mm, 37 parts (0 on the bottom side), 27 nets.

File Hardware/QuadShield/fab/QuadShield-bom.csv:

"Reference","Value","Footprint","LCSC","Description","QUANTITY","DNP"
"BZ1","Buzzer 5V","Buzzer_Beeper:Buzzer_12x9.5RM7.6","","active buzzer, + = pin 1","1",""
"C1","10uF 35V","Capacitor_SMD:C_1206_3216Metric","","buck input","1",""
"C2","100nF 50V","Capacitor_SMD:C_0603_1608Metric","","buck input HF","1",""
"C3,C7","100nF","Capacitor_SMD:C_0603_1608Metric","","-- mixed values --","2",""
"C4,C5","22uF 10V","Capacitor_SMD:C_1206_3216Metric","","buck output","2",""
"C6","10uF 10V","Capacitor_SMD:C_0805_2012Metric","","5V rail","1",""
"D1,D2","SS34","Diode_SMD:D_SMA","","-- mixed values --","2",""
"D3","LED green","LED_SMD:LED_0603_1608Metric","","K=1, A=2","1",""
"D4","1N4148W","Diode_SMD:D_SOD-123","","flyback, K=1","1",""
"F1","1.5A PTC","Fuse:Fuse_1812_4532Metric","","resettable fuse","1",""
"J1","DISC1 P1","Connector_PinHeader_2.54mm:PinHeader_2x32_P2.54mm_Vertical","","2x32 FEMALE socket; PinHeader pad pattern on purpose (KiCad PinSocket is mirrored: pin2 at -x)","1",""
"J2","DISC1 P2","Connector_PinHeader_2.54mm:PinHeader_2x32_P2.54mm_Vertical","","2x32 FEMALE socket; PinHeader pad pattern on purpose (KiCad PinSocket is mirrored: pin2 at -x)","1",""
"J3","XT30 battery","Connector_AMASS:AMASS_XT30PW-M_1x02_P2.50mm_Horizontal","","2S-4S LiPo, pin 1 = +","1",""
"J4","ESC M1","Connector_PinHeader_2.54mm:PinHeader_1x03_P2.54mm_Vertical","","M1 front-left, middle pin open","1",""
"J5","ESC M2","Connector_PinHeader_2.54mm:PinHeader_1x03_P2.54mm_Vertical","","M2 back-left","1",""
"J6","ESC M3","Connector_PinHeader_2.54mm:PinHeader_1x03_P2.54mm_Vertical","","M3 front-right","1",""
"J7","ESC M4","Connector_PinHeader_2.54mm:PinHeader_1x03_P2.54mm_Vertical","","M4 back-right","1",""
"J8","GY-521","Connector_PinHeader_2.54mm:PinHeader_1x08_P2.54mm_Vertical","","AD0 = GND -> address 0x68; X arrow to the TAIL","1",""
"J9","GPS","Connector_PinHeader_2.54mm:PinHeader_1x06_P2.54mm_Vertical","","GPS TX -> PD2, GPS RX <- PC12, compass on I2C2","1",""
"J10","RC CH1","Connector_PinHeader_2.54mm:PinHeader_1x03_P2.54mm_Vertical","","receiver channel (RC FULL build)","1",""
"J11","RC CH2","Connector_PinHeader_2.54mm:PinHeader_1x03_P2.54mm_Vertical","","receiver channel (RC FULL build)","1",""
"J12","RC CH3","Connector_PinHeader_2.54mm:PinHeader_1x03_P2.54mm_Vertical","","receiver channel (RC FULL build)","1",""
"J13","RC CH4","Connector_PinHeader_2.54mm:PinHeader_1x03_P2.54mm_Vertical","","receiver channel (RC FULL build)","1",""
"J14","RC CH5","Connector_PinHeader_2.54mm:PinHeader_1x03_P2.54mm_Vertical","","receiver channel (RC FULL build)","1",""
"L1","4.7uH 3A","Inductor_SMD:L_Taiyo-Yuden_NR-50xx","","shielded, Isat >= 3 A","1",""
"Q1","MMBT3904","Package_TO_SOT_SMD:SOT-23","","B=1 E=2 C=3","1",""
"R1","2k2","Resistor_SMD:R_0603_1608Metric","","power LED","1",""
"R2","100k","Resistor_SMD:R_0603_1608Metric","","divider top","1",""
"R3","22k","Resistor_SMD:R_0603_1608Metric","","divider bottom","1",""
"R4","1k","Resistor_SMD:R_0603_1608Metric","","base","1",""
"R5","10k","Resistor_SMD:R_0603_1608Metric","","keeps it off at reset","1",""
"R6,R7","4k7 DNP","Resistor_SMD:R_0603_1608Metric","","optional pull-up","2","DNP"
"U1","AP63205WU-7","Package_TO_SOT_SMD:TSOT-23-6","C2071056","FB=VOUT, EN=VIN (DS41326 fig.1)","1",""

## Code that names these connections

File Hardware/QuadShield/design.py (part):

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  MPU6050 I2C2: SDA PF0 (P1-7), SCL PF1 (P1-8)
  GPS UART5: MCU TX PC12 (P1-43) -> GPS RX, MCU RX PD2 (P1-40) <- GPS TX
  RC: PE2 (P1-15) PE3 (P1-16) PE4 (P1-13) PE5 (P1-14) PE6 (P1-11)
  Battery sense ADC: PC3 (P2-15, ADC123_IN13)   Buzzer: PD4 (P1-38)
  Power: 5V into P1-1 / P1-2 (UM1670 6.4: 5 V pins may be used as input),
         3V (P2-1 / P2-2) used as 3.3 V supply for the MPU (output, <100 mA)
         GND P1-63/64, P2-11/29/63
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# MCU pin name -> shield net name (only the pins the shield uses)
MCU_NETS = {
    "5V": "+5V", "3V": "+3V3", "GND": "GND",
    "PB4": "ESC1", "PA8": "ESC2", "PB0": "ESC3", "PB10": "ESC4",
    "PF0": "I2C_SDA", "PF1": "I2C_SCL",
    "PC12": "GPS_RX", "PD2": "GPS_TX",          # names from the GPS side
    "PE2": "RC1", "PE3": "RC2", "PE4": "RC3", "PE5": "RC4", "PE6": "RC5",
    "PC3": "VBAT_SENSE", "PD4": "BUZZER",
}

# ---------------------------------------------------------------------------
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    # Battery input + protection + 5 V buck
    "J3": ("XT30 battery", "Connector_Generic:Conn_01x02",
           "Connector_AMASS:AMASS_XT30PW-M_1x02_P2.50mm_Horizontal",
           {1: "VBAT_RAW", 2: "GND"}, "", "2S-4S LiPo, pin 1 = +"),
    "F1": ("1.5A PTC", "Device:Polyfuse", "Fuse:Fuse_1812_4532Metric",
           {1: "VBAT_RAW", 2: "VBAT_F"}, "", "resettable fuse"),
    "D1": ("SS34", "Device:D_Schottky", "Diode_SMD:D_SMA",
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
    # Buzzer: active 5 V buzzer, low-side NPN
    "BZ1": ("Buzzer 5V", "Device:Buzzer", "Buzzer_Beeper:Buzzer_12x9.5RM7.6",
            {1: "+5V", 2: "BZ_N"}, "", "active buzzer, + = pin 1"),
    "Q1": ("MMBT3904", "Transistor_BJT:MMBT3904", "Package_TO_SOT_SMD:SOT-23",
           {1: "BZ_B", 2: "GND", 3: "BZ_N"}, "", "B=1 E=2 C=3"),
    "R4": ("1k", "Device:R", "Resistor_SMD:R_0603_1608Metric",
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    # ESC outputs: signal / NC (red BEC wire) / GND
    "J4": ("ESC M1", "Connector_Generic:Conn_01x03",
           "Connector_PinHeader_2.54mm:PinHeader_1x03_P2.54mm_Vertical",
           {1: "ESC1", 3: "GND"}, "", "M1 front-left, middle pin open"),
    "J5": ("ESC M2", "Connector_Generic:Conn_01x03",
           "Connector_PinHeader_2.54mm:PinHeader_1x03_P2.54mm_Vertical",
           {1: "ESC2", 3: "GND"}, "", "M2 back-left"),
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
